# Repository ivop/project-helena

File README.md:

# project-helena
Atari XL keyboard replacement

Note that this board is untested so far. But what can go wrong with a bunch of switches? :)

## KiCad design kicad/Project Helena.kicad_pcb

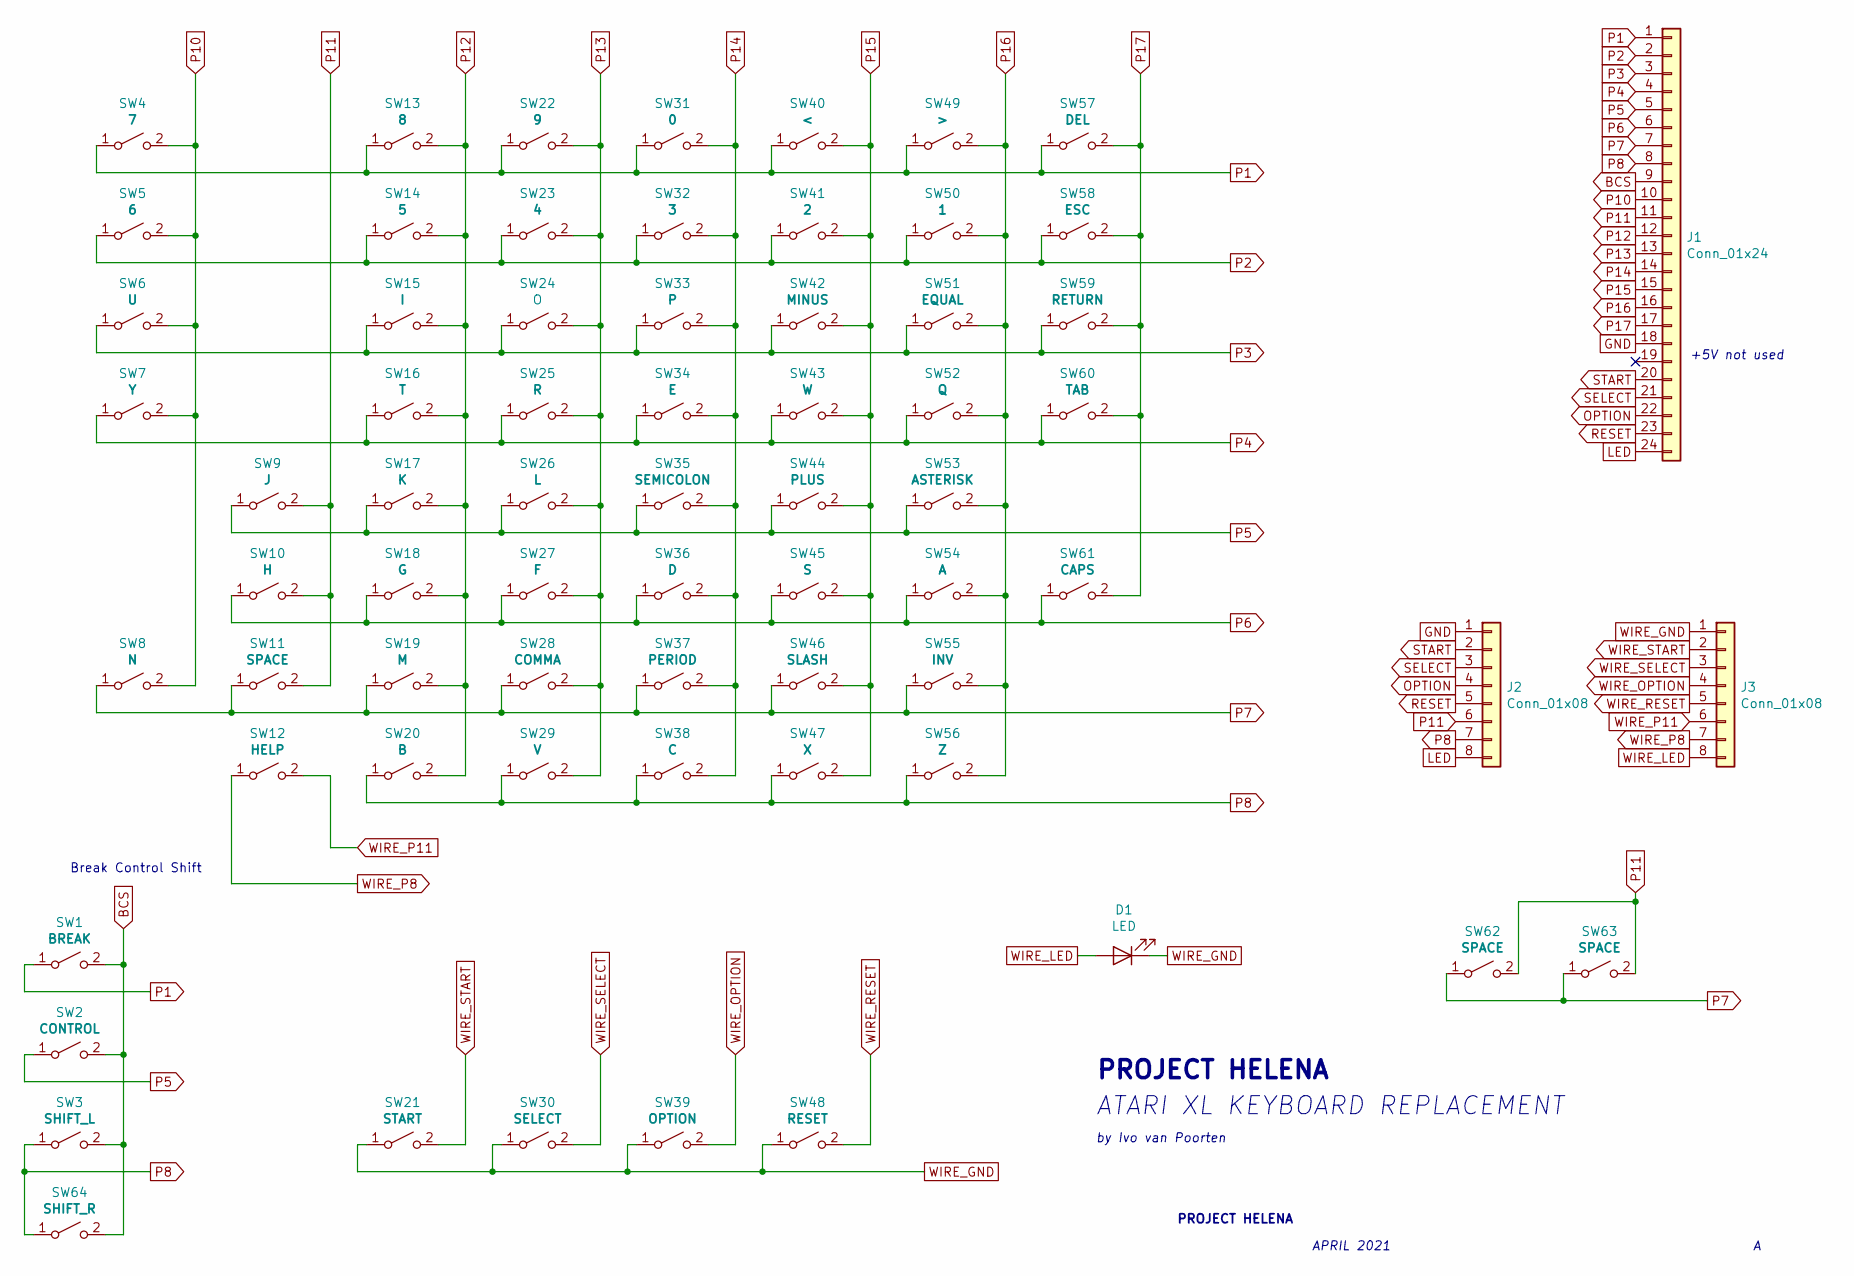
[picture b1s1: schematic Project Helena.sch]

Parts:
D1: LED; LED_D5.0mm
J1: Conn_01x24; PinHeader_1x24_P2.54mm_Vertical
J2, J3: Conn_01x08; PinHeader_1x08_P2.54mm_Vertical
SW1: BREAK; SW_Cherry_MX1A_1.00u_Plate
SW2: CONTROL; SW_Cherry_MX1A_2.00u_Plate
SW3: SHIFT_L; SW_Cherry_MX1A_1.50u_Plate
SW4: 7; SW_Cherry_MX1A_1.00u_Plate
SW5: 6; SW_Cherry_MX1A_1.00u_Plate
SW6: U; SW_Cherry_MX1A_1.00u_Plate
SW7: Y; SW_Cherry_MX1A_1.00u_Plate
SW8: N; SW_Cherry_MX1A_1.00u_Plate
SW9: J; SW_Cherry_MX1A_1.00u_Plate
SW10: H; SW_Cherry_MX1A_1.00u_Plate
SW11, SW62, SW63: SPACE; SW_Cherry_MX1A_1.00u_Plate
SW12: HELP; SW_Cherry_MX1A_1.00u_Plate
SW13: 8; SW_Cherry_MX1A_1.00u_Plate
SW14: 5; SW_Cherry_MX1A_1.00u_Plate
SW15: I; SW_Cherry_MX1A_1.00u_Plate
SW16: T; SW_Cherry_MX1A_1.00u_Plate
SW17: K; SW_Cherry_MX1A_1.00u_Plate
SW18: G; SW_Cherry_MX1A_1.00u_Plate
SW19: M; SW_Cherry_MX1A_1.00u_Plate
SW20: B; SW_Cherry_MX1A_1.00u_Plate
SW21: START; SW_Cherry_MX1A_1.00u_Plate
SW22: 9; SW_Cherry_MX1A_1.00u_Plate
SW23: 4; SW_Cherry_MX1A_1.00u_Plate
SW24: O; SW_Cherry_MX1A_1.00u_Plate
SW25: R; SW_Cherry_MX1A_1.00u_Plate
SW26: L; SW_Cherry_MX1A_1.00u_Plate
SW27: F; SW_Cherry_MX1A_1.00u_Plate
SW28: COMMA; SW_Cherry_MX1A_1.00u_Plate
SW29: V; SW_Cherry_MX1A_1.00u_Plate
SW30: SELECT; SW_Cherry_MX1A_1.00u_Plate
SW31: 0; SW_Cherry_MX1A_1.00u_Plate
SW32: 3; SW_Cherry_MX1A_1.00u_Plate
SW33: P; SW_Cherry_MX1A_1.00u_Plate
SW34: E; SW_Cherry_MX1A_1.00u_Plate
SW35: SEMICOLON; SW_Cherry_MX1A_1.00u_Plate
SW36: D; SW_Cherry_MX1A_1.00u_Plate
SW37: PERIOD; SW_Cherry_MX1A_1.00u_Plate
SW38: C; SW_Cherry_MX1A_1.00u_Plate
SW39: OPTION; SW_Cherry_MX1A_1.00u_Plate
SW40: <; SW_Cherry_MX1A_1.00u_Plate
SW41: 2; SW_Cherry_MX1A_1.00u_Plate
SW42: MINUS; SW_Cherry_MX1A_1.00u_Plate
SW43: W; SW_Cherry_MX1A_1.00u_Plate
SW44: PLUS; SW_Cherry_MX1A_1.00u_Plate
SW45: S; SW_Cherry_MX1A_1.00u_Plate
SW46: SLASH; SW_Cherry_MX1A_1.00u_Plate
SW47: X; SW_Cherry_MX1A_1.00u_Plate
SW48: RESET; SW_Cherry_MX1A_1.00u_Plate
SW49: >; SW_Cherry_MX1A_1.00u_Plate
SW50: 1; SW_Cherry_MX1A_1.00u_Plate
SW51: EQUAL; SW_Cherry_MX1A_1.00u_Plate
SW52: Q; SW_Cherry_MX1A_1.00u_Plate
SW53: ASTERISK; SW_Cherry_MX1A_1.00u_Plate
SW54: A; SW_Cherry_MX1A_1.00u_Plate
SW55: INV; SW_Cherry_MX1A_1.00u_Plate
SW56: Z; SW_Cherry_MX1A_1.00u_Plate
SW57: DEL; SW_Cherry_MX1A_1.00u_Plate
SW58: ESC; SW_Cherry_MX1A_1.25u_Plate
SW59: RETURN; SW_Cherry_MX1A_1.50u_Plate
SW60: TAB; SW_Cherry_MX1A_1.75u_Plate
SW61: CAPS; SW_Cherry_MX1A_1.25u_Plate
SW64: SHIFT_R; SW_Cherry_MX1A_1.75u_Plate

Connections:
BCS: J1.9, SW1.2 (B), SW2.2 (B), SW3.2 (B), SW64.2 (B)
GND: J1.18, J2.1
LED: J1.24, J2.8
OPTION: J1.22, J2.4
P1: J1.1, SW1.1 (A), SW4.1 (A), SW13.1 (A), SW22.1 (A), SW31.1 (A), SW40.1 (A), SW49.1 (A), SW57.1 (A)
P2: J1.2, SW5.1 (A), SW14.1 (A), SW23.1 (A), SW32.1 (A), SW41.1 (A), SW50.1 (A), SW58.1 (A)
P3: J1.3, SW6.1 (A), SW15.1 (A), SW24.1 (A), SW33.1 (A), SW42.1 (A), SW51.1 (A), SW59.1 (A)
P4: J1.4, SW7.1 (A), SW16.1 (A), SW25.1 (A), SW34.1 (A), SW43.1 (A), SW52.1 (A), SW60.1 (A)
P5: J1.5, SW2.1 (A), SW9.1 (A), SW17.1 (A), SW26.1 (A), SW35.1 (A), SW44.1 (A), SW53.1 (A)
P6: J1.6, SW10.1 (A), SW18.1 (A), SW27.1 (A), SW36.1 (A), SW45.1 (A), SW54.1 (A), SW61.1 (A)
P7: J1.7, SW8.1 (A), SW11.1 (A), SW19.1 (A), SW28.1 (A), SW37.1 (A), SW46.1 (A), SW55.1 (A), SW62.1 (A), SW63.1 (A)
P8: J1.8, J2.7, SW3.1 (A), SW20.1 (A), SW29.1 (A), SW38.1 (A), SW47.1 (A), SW56.1 (A), SW64.1 (A)
P10: J1.10, SW4.2 (B), SW5.2 (B), SW6.2 (B), SW7.2 (B), SW8.2 (B)
P11: J1.11, J2.6, SW9.2 (B), SW10.2 (B), SW11.2 (B), SW62.2 (B), SW63.2 (B)
P12: J1.12, SW13.2 (B), SW14.2 (B), SW15.2 (B), SW16.2 (B), SW17.2 (B), SW18.2 (B), SW19.2 (B), SW20.2 (B)
P13: J1.13, SW22.2 (B), SW23.2 (B), SW24.2 (B), SW25.2 (B), SW26.2 (B), SW27.2 (B), SW28.2 (B), SW29.2 (B)
P14: J1.14, SW31.2 (B), SW32.2 (B), SW33.2 (B), SW34.2 (B), SW35.2 (B), SW36.2 (B), SW37.2 (B), SW38.2 (B)
P15: J1.15, SW40.2 (B), SW41.2 (B), SW42.2 (B), SW43.2 (B), SW44.2 (B), SW45.2 (B), SW46.2 (B), SW47.2 (B)
P16: J1.16, SW49.2 (B), SW50.2 (B), SW51.2 (B), SW52.2 (B), SW53.2 (B), SW54.2 (B), SW55.2 (B), SW56.2 (B)
P17: J1.17, SW57.2 (B), SW58.2 (B), SW59.2 (B), SW60.2 (B), SW61.2 (B)
RESET: J1.23, J2.5
SELECT: J1.21, J2.3
START: J1.20, J2.2
WIRE_GND: D1.1 (K), J3.1, SW21.1 (A), SW30.1 (A), SW39.1 (A), SW48.1 (A)
WIRE_LED: D1.2 (A), J3.8
WIRE_OPTION: J3.4, SW39.2 (B)
WIRE_P8: J3.7, SW12.1 (A)
WIRE_P11: J3.6, SW12.2 (B)
WIRE_RESET: J3.5, SW48.2 (B)
WIRE_SELECT: J3.3, SW30.2 (B)
WIRE_START: J3.2, SW21.2 (B)

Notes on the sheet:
Break Control Shift
+5V not used
PROJECT HELENA
ATARI XL KEYBOARD REPLACEMENT
by Ivo van Poorten
APRIL 2021

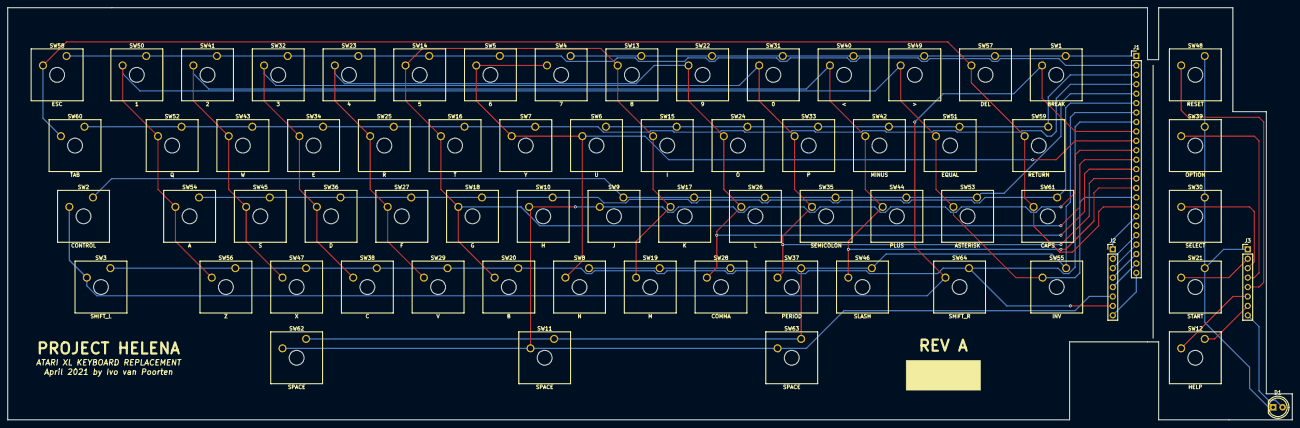
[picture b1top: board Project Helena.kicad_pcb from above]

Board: 2 copper layers, 346.0 x 111.0 mm, 68 parts (0 on the bottom side), 31 nets.

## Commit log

2021-04-17 version one
2021-04-17 schematic
2021-04-18 add labels for BCS and SSOR.
2021-04-22 first revision of PCB
2021-04-22 hide some layers, prepare for proper silkscreen
2021-04-23 update silkscreen!
2021-04-23 update of PCB and raytraced image
2021-04-26 add field for serial number and generate gerbers
